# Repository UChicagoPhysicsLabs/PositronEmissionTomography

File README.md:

# Positron Emission Tomography
Code and schematics for a positron emission tomography experiment for upper-division physics laboratories

A bill of materials is kept at the following link: https://docs.google.com/spreadsheets/d/1UGA9dp_g9l_pHDlyD9L5UesSFoDoISthVe1psVAu_JQ/

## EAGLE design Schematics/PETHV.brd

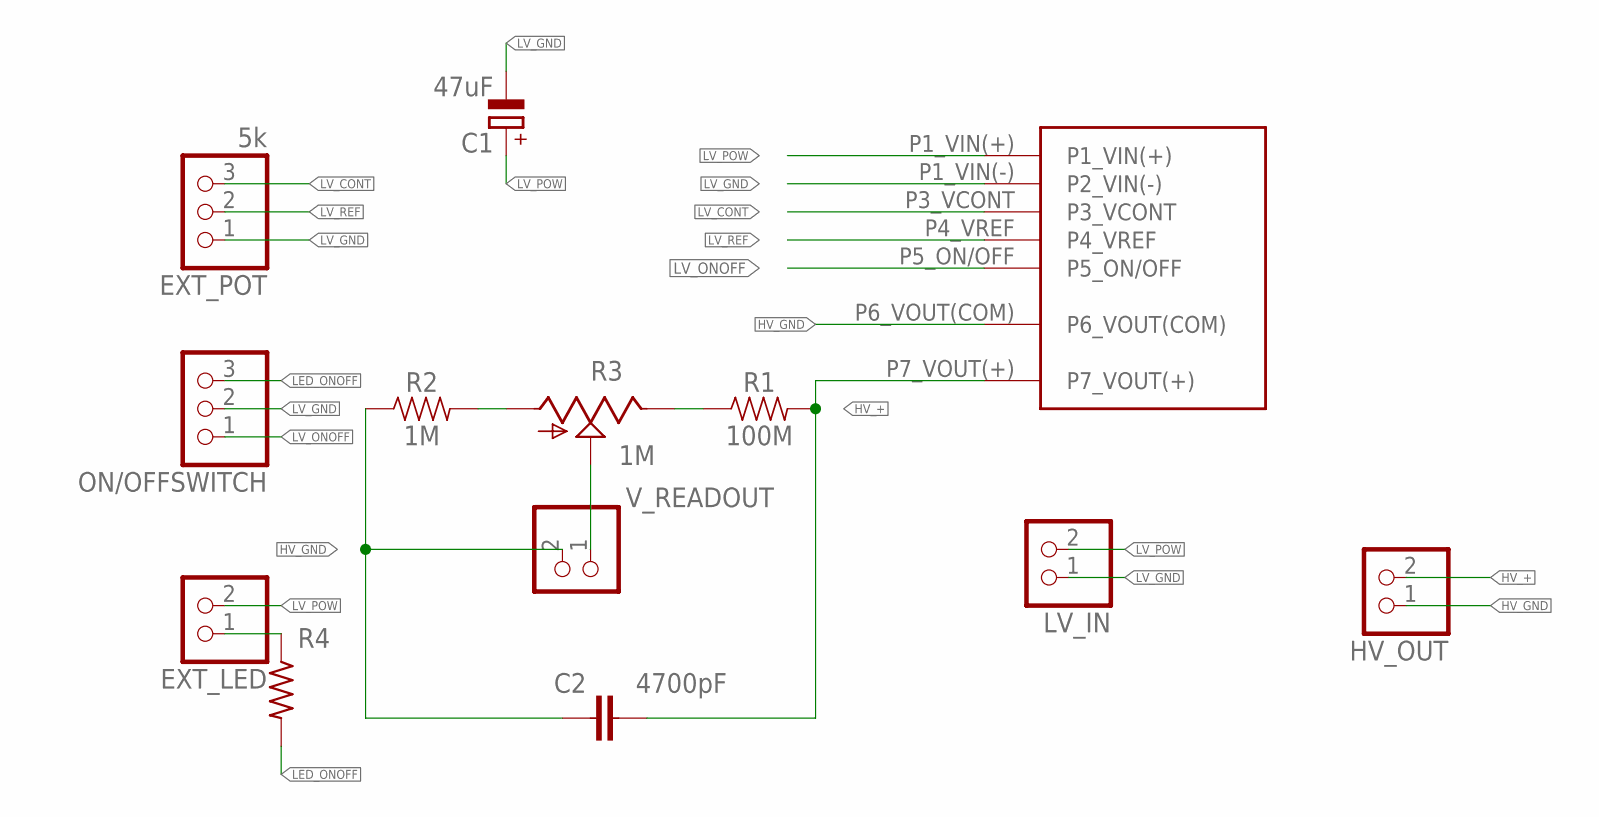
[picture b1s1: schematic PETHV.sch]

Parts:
C1: 47uF; E2,5-5
C2: 4700pF; C2.5-5
EXT_LED: PINHD-1X2; 1X02
EXT_POT: 5k; 1X03
HV_OUT: PINHD-1X2; 1X02
LV_IN: PINHD-1X2; 1X02
ON/OFFSWITCH: PINHD-1X3; 1X03
R1: 100M; AXIAL-0.3
R2: 1M; AXIAL-0.3
R3: 1M; B25P
R4: R-US_0204/7; 0204/7
U$1: BELLNIX-MHV122.0K1000P; BELLNIX-MHV12
V_READOUT: PINHD-1X2; 1X02

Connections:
HV_+: C2.2, HV_OUT.2, R1.P$2 (2), U$1.P7_VOUT(+)
HV_GND: C2.1, HV_OUT.1, R2.P$1 (1), U$1.P6_VOUT(COM), V_READOUT.2
LED_ONOFF: ON/OFFSWITCH.3, R4.2
LV_CONT: EXT_POT.3, U$1.P3_VCONT
LV_GND: C1.-, EXT_POT.1, LV_IN.1, ON/OFFSWITCH.2, U$1.P1_VIN(-) (P2_VIN(-))
LV_ONOFF: ON/OFFSWITCH.1, U$1.P5_ON/OFF
LV_POW: C1.+, EXT_LED.2, LV_IN.2, U$1.P1_VIN(+)
LV_REF: EXT_POT.2, U$1.P4_VREF
unnamed: R2.P$2 (2), R3.A
unnamed: EXT_LED.1, R4.1
unnamed: R1.P$1 (1), R3.E
unnamed: R3.S, V_READOUT.1

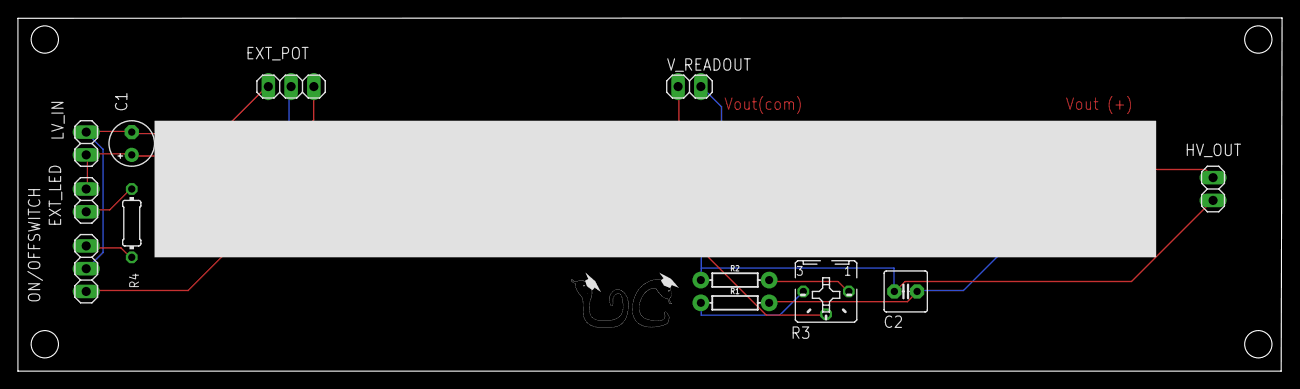
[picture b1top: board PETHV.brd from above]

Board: 2 copper layers, 141.1 x 39.4 mm, 13 parts (0 on the bottom side), 12 nets.

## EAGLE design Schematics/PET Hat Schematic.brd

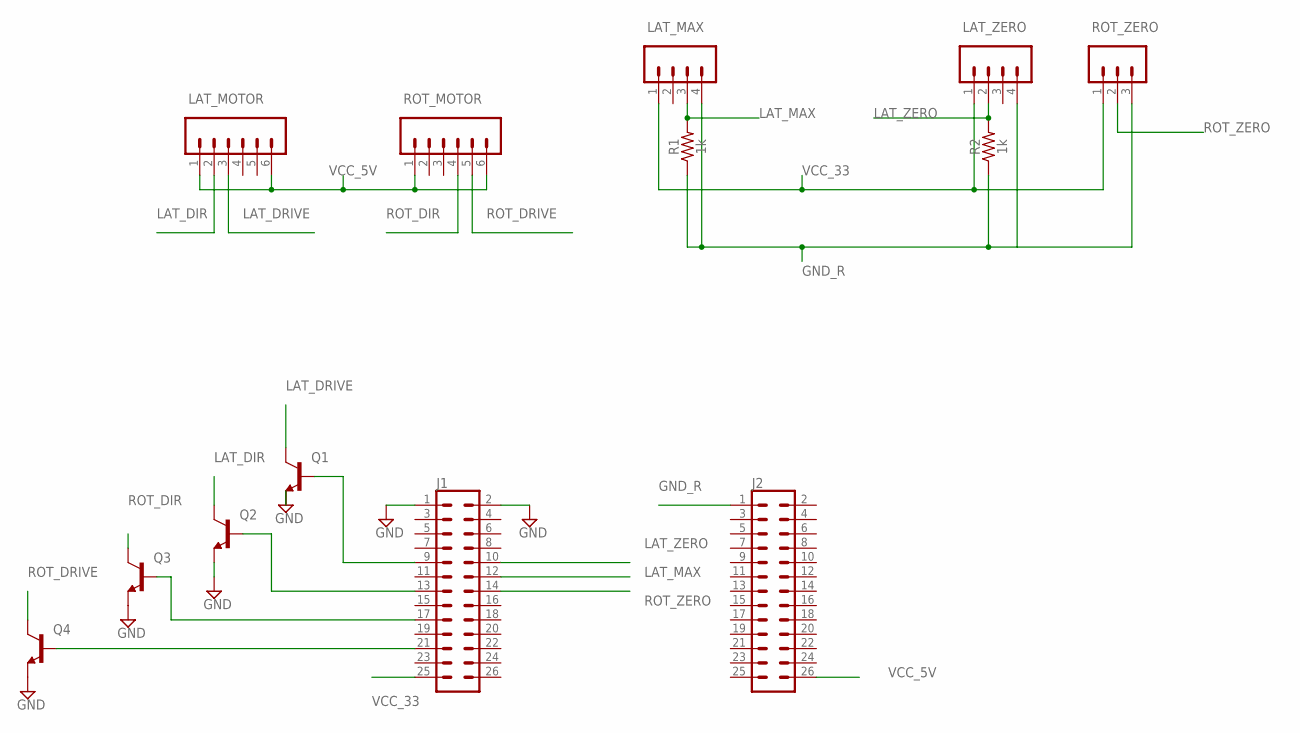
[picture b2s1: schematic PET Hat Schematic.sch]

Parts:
J1, J2: CONN_13X22X13; 2X13
LAT_MAX: CONN_04POLAR; MOLEX-1X4
LAT_MOTOR: CONN_06POLAR; MOLEX-1X6
LAT_ZERO: CONN_04POLAR; MOLEX-1X4
Q1, Q2, Q3, Q4: 2N3904; TO92
R1, R2: 1k; AXIAL-0.3
ROT_MOTOR: CONN_06POLAR; MOLEX-1X6
ROT_ZERO: CONN_03POLAR; MOLEX-1X3

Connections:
GND: J1.1, J1.2, Q1.3 (E), Q2.3 (E), Q3.3 (E), Q4.3 (E)
GND_R: J2.1, LAT_MAX.4, R1.P$1 (1), R2.P$1 (1), ROT_ZERO.3
GND_RIGHT: LAT_ZERO.4
LAT_DIR: LAT_MOTOR.2, Q2.1 (C)
LAT_DRIVE: LAT_MOTOR.3, Q1.1 (C)
LAT_MAX: J1.12, LAT_MAX.3, R1.P$2 (2)
LAT_ZERO: J1.10, LAT_ZERO.2, R2.P$2 (2)
unnamed: J1.9, Q1.2 (B)
unnamed: J1.13, Q2.2 (B)
unnamed: J1.17, Q3.2 (B)
unnamed: J1.21, Q4.2 (B)
ROT_DIR: Q3.1 (C), ROT_MOTOR.4
ROT_DRIVE: Q4.1 (C), ROT_MOTOR.5
ROT_ZERO: J1.14, ROT_ZERO.2
VCC_5V: J2.26, LAT_MOTOR.1, LAT_MOTOR.6, ROT_MOTOR.1, ROT_MOTOR.6
VCC_33: J1.25, LAT_MAX.1, LAT_ZERO.1, ROT_ZERO.1

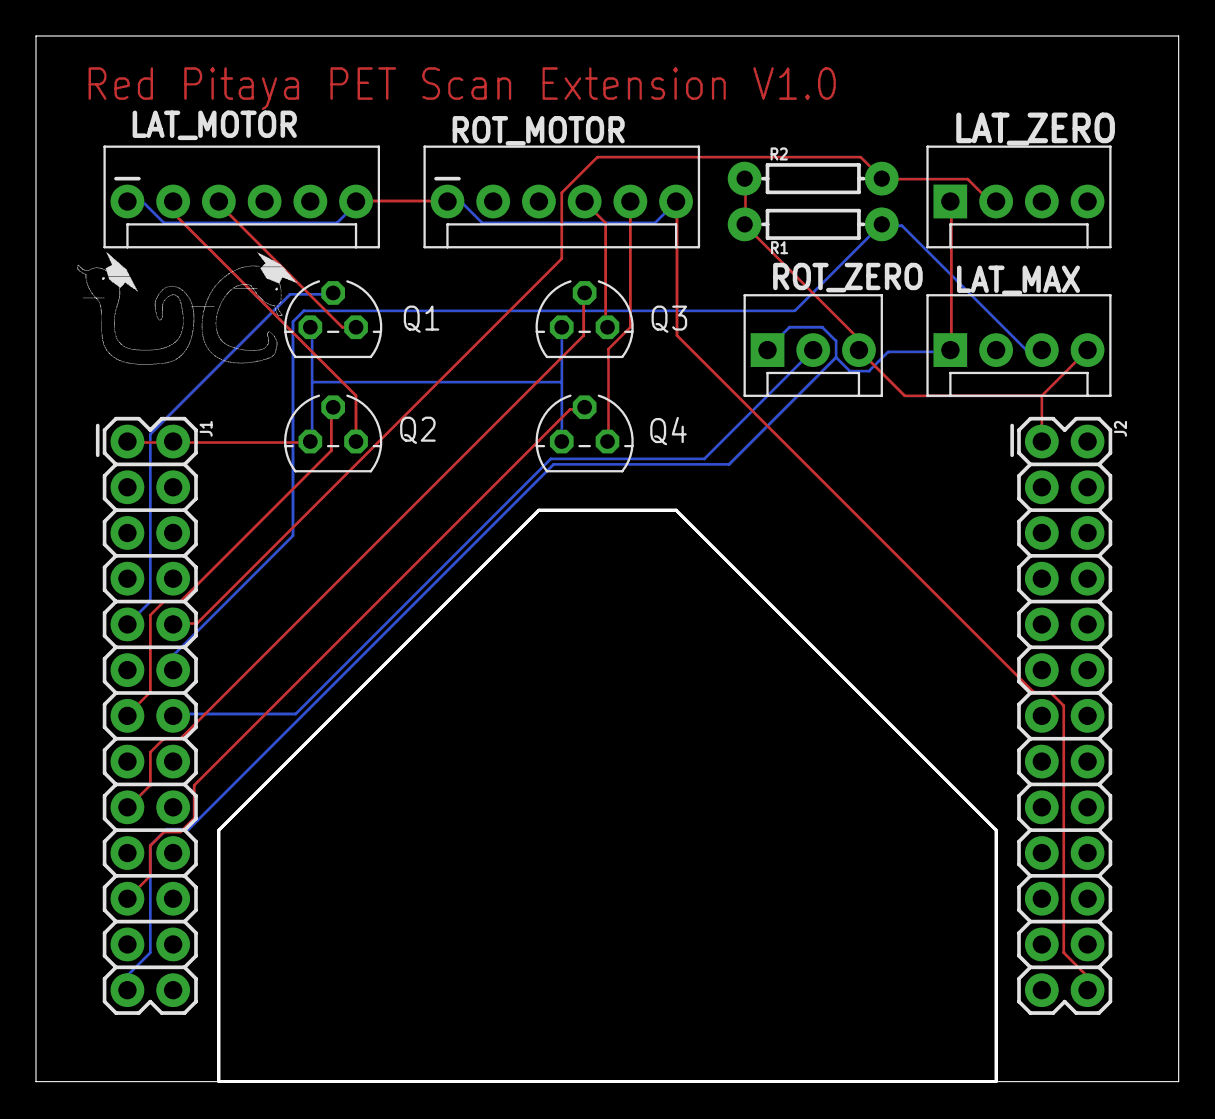
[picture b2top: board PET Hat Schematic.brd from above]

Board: 2 copper layers, 63.3 x 58.0 mm, 13 parts (0 on the bottom side), 15 nets.

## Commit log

2022-11-04 First attempt at aggregating all materials under GitHub.
2023-04-26 Uploaded Vivado files
    Uploaded build script for generating Vivado project. Tested only on a single Windows machine, so ymmv.
2023-04-26 Create system_wrapper.bit
    A currently working compiled version of the FPGA code.
2023-05-23 readthedocs.io documentation outline created
2023-05-23 Created doc file structure
2023-05-23 Documentation update
2023-05-23 More documentation updates
2023-05-25 Fixed issue in build.tcl to make compatible with new Vivado instillations
2023-05-25 Documentation Upgrades
2023-05-26 Table fix hopefully
2023-05-26 Title fixes
2023-05-26 Table tweaks
2023-05-26 css tweaks
2023-05-26 css again
2023-06-13 Moved actual Gerber files to directory
2023-06-13 Added schematic of PET hat
2023-06-22 Updating documentation
2023-06-29 Update of Python Code
2023-06-29 Update of schematics
2023-07-06 Massive update to getting started instructions
2023-07-07 Added starting page to index
2023-07-07 Format tweaks
2023-07-07 formatting
2023-07-07 more fixes >.<
2023-07-07 testing title fixes
2023-07-07 Fixes after finding error messages from Sphinx didn't show up by default when compiling new page.
2023-07-07 more tweaks
2023-07-07 Uploaded stl files
2023-07-07 More lembas bread
2025-05-20 Update README.md
    PCB link was broken, removed
2025-07-14 Complete rewrite of FPGA code
    FPGA code re-written from scratch. Not backwards compatible.
2025-07-14 fixing docs
2025-07-14 fixing docs still
2025-07-14 still fixing docs
2025-07-14 Updating stl files
2025-07-14 Documentation updates
2025-07-15 Updated plotting notebook
2025-07-15 renamed directories to make Vivado happy
2025-07-15 Added board file for Vivado

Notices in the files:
parts and their libraries:
SparkFun-Connectors: Licensing: Creative Commons ShareAlike 4.0 International - https://creativecommons.org/licenses/by-sa/4.0
